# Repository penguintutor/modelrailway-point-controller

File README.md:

# Model railway point controller

The model railway point controller provides a way to control up to 4 points using a Raspberry Pi Pico W. It includes a MOSFET based capacitor discharge unit on the PCB and MOSFET controllers for each of the point motors.

It includes a second control board connected by I2C which can be connected to physical LEDs and switches to provide a way to control the points. The points can also be controlled using a web interface which can also be used in conjunction with GUI software to provide a touch screen interface.

# Installation

This version needs to be installed on a Raspberry Pi Pico W with the appropriate network enabled MicroPython. MicroPython can be installed through the Thonny editor.

To install the program, copy all the files in the pico-src directory to the top-level of the Raspberry Pi Pico. For the network connection you also need to create a file called secrets.py with details of your SSID and PASSWORD. The example below shows the formatting for the secrets.py file.

    SSID="NetworkSSID"
    PASSWORD="WiFiPassword"
    
## Configuration

The program can be run in two modes. 

* Access Point Mode (AP mode) - In this mode the Pico will act as a Wireless Access Point which you can connect to using another WiFi enabled device.
* Client Mode - In this mode you can connect to an existing wireless network

Note that in client mode it is currently blocking and will not operate until it has successfully connected to the network.

The mode is set by editing the entry "mode" in the pico-lights.py file. 

mode="ap"       # Use as an access point
mode="client"   # Use as a Wi-Fi client

## Running on startup

For the code to run automatically on start-up save the pico-point-controller.py file on your Pico as main.py.

## Using without the I2C control board

The board can be used in WiFi only mode, which does not use the I2C based switch and LED board. For that use the file pico-point-controller.wifionly.py instead of pico-point-controller.py (or save as main.py for auto-run) 

# More Information

For more details see [www.penguintutor.com/points](https://www.penguintutor.com/points)

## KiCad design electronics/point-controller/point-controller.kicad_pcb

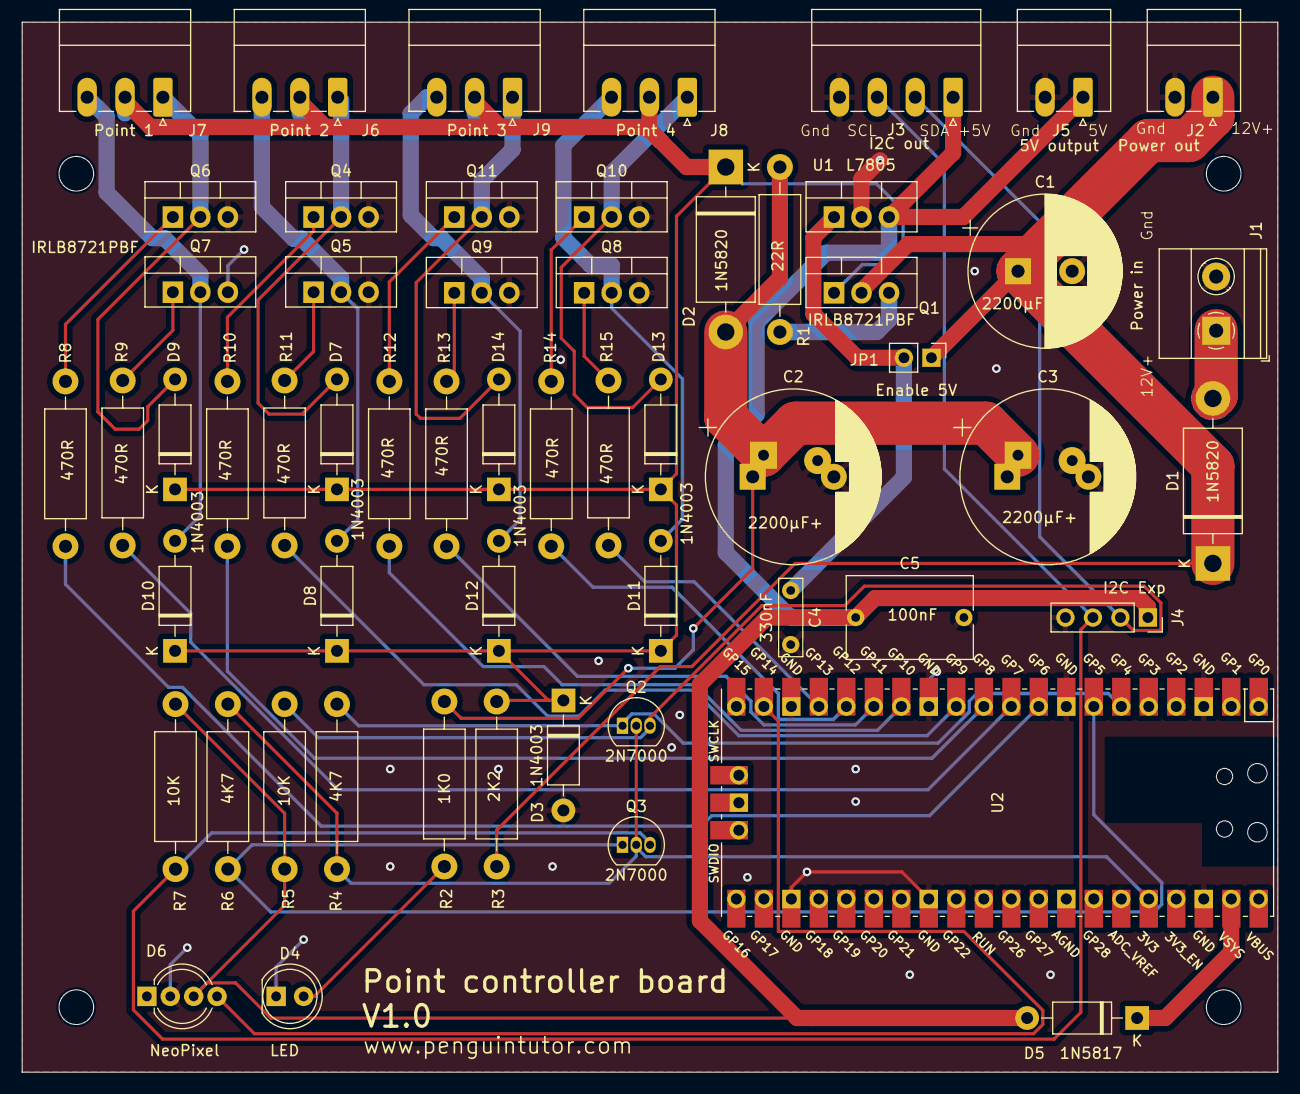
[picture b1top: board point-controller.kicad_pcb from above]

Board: 2 copper layers, 116.0 x 97.0 mm, 61 parts (0 on the bottom side), 40 nets.

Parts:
C1: 2200μF; CP_Radial_D14.0mm_P5.00mm
C2, C3: 2200μF+; CP_Radial_D16.0mm_P7.50mm_P5.00mm
C4: 330nF; C_Rect_L7.0mm_W2.0mm_P5.00mm
C5: 100nF; C_Rect_L11.5mm_W7.5mm_P10.00mm_MKT
D1, D2: 1N5820; D_DO-201AD_P15.24mm_Horizontal
D3, D7, D8, D9, D10, D11, D12, D13, D14: 1N4003; D_DO-41_SOD81_P10.16mm_Horizontal
D4: LED; LED_D5.0mm
D5: 1N5817; D_DO-41_SOD81_P10.16mm_Horizontal
D6: NeoPixel; LED_D5.0mm-4_RGB_Wide_Pins
H1, H2, H3, H4: MountingHole; MountingHole_3.2mm_M3
J1: Power in; TerminalBlock_Phoenix_MKDS-1,5-2_1x02_P5.00mm_Horizontal
J2: Power out; PhoenixContact_MC_1,5_2-G-3.5_1x02_P3.50mm_Horizontal
J3: I2C out; PhoenixContact_MC_1,5_4-G-3.5_1x04_P3.50mm_Horizontal
J4: I2C Exp; PinSocket_1x04_P2.54mm_Vertical
J5: 5V output; PhoenixContact_MC_1,5_2-G-3.5_1x02_P3.50mm_Horizontal
J6: Point 2; PhoenixContact_MC_1,5_3-G-3.5_1x03_P3.50mm_Horizontal
J7: Point 1; PhoenixContact_MC_1,5_3-G-3.5_1x03_P3.50mm_Horizontal
J8: Point 4; PhoenixContact_MC_1,5_3-G-3.5_1x03_P3.50mm_Horizontal
J9: Point 3; PhoenixContact_MC_1,5_3-G-3.5_1x03_P3.50mm_Horizontal
JP1: Enable 5V; PinHeader_1x02_P2.54mm_Vertical
Q1, Q4, Q5, Q6, Q7, Q8, Q9, Q10, Q11: IRLB8721PBF; TO-220-3_Vertical
Q2, Q3: 2N7000; TO-92_Inline
R1: 22R; R_Axial_DIN0411_L9.9mm_D3.6mm_P15.24mm_Horizontal
R2: 1K0; R_Axial_DIN0411_L9.9mm_D3.6mm_P15.24mm_Horizontal
R3: 2K2; R_Axial_DIN0411_L9.9mm_D3.6mm_P15.24mm_Horizontal
R4, R6: 4K7; R_Axial_DIN0411_L9.9mm_D3.6mm_P15.24mm_Horizontal
R5, R7: 10K; R_Axial_DIN0411_L9.9mm_D3.6mm_P15.24mm_Horizontal
R8, R9, R10, R11, R12, R13, R14, R15: 470R; R_Axial_DIN0411_L9.9mm_D3.6mm_P15.24mm_Horizontal
U1: L7805; TO-220-3_Vertical
U2: Pico; RPi_Pico_SMD_TH

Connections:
+3.3V: Q2.2 (G), Q3.2 (G), R4.1, R6.1, U2.36 (3V3)
+5V: C5.1, D5.2 (A), D6.3 (VDD), J3.1, J4.1, J5.1, R5.1, R7.1, U1.3 (OUT)
+12V: C1.1, D1.1 (K), J2.1, JP1.1 (A), Q1.2 (D), R3.1
CDU: D2.1 (K), D3.1 (K), D7.1 (K), D8.1 (K), D9.1 (K), D10.1 (K), D11.1 (K), D12.1 (K), D13.1 (K), D14.1 (K), J6.2, J7.2, J8.2, J9.2, Q1.1 (G), R3.2
GND: C1.2, C2.2, C3.2, C4.2, C5.2, D3.2 (A), D4.1 (K), D6.2 (GND), J1.2, J2.2, J3.4, J4.4, J5.2, Q4.3 (S), Q5.3 (S), Q6.3 (S), Q7.3 (S), Q8.3 (S), Q9.3 (S), Q10.3 (S), Q11.3 (S), U1.2 (GND), U2.3 (GND), U2.8 (GND), U2.13 (GND), U2.18 (GND), U2.23 (GND), U2.28 (GND), U2.38 (GND)
I2C 5V SCL: J3.3, J4.3, Q3.3 (D), R7.2
I2C 5V SDA: J3.2, J4.2, Q2.3 (D), R5.2
I2C SCL: Q3.1 (S), R6.2, U2.7 (GPIO5)
I2C SDA: Q2.1 (S), R4.2, U2.6 (GPIO4)
unnamed: D1.2 (A), J1.1
unnamed: C2.1, C3.1, D2.2 (A), R1.2, R2.1
unnamed: D4.2 (A), R2.2
unnamed: D5.1 (K), U2.39 (VSYS)
unnamed: D7.2 (A), J6.1, Q4.2 (D)
unnamed: D8.2 (A), J6.3, Q5.2 (D)
unnamed: D9.2 (A), J7.1, Q6.2 (D)
unnamed: D10.2 (A), J7.3, Q7.2 (D)
unnamed: D11.2 (A), J8.3, Q8.2 (D)
unnamed: D12.2 (A), J9.3, Q9.2 (D)
unnamed: D13.2 (A), J8.1, Q10.2 (D)
unnamed: D14.2 (A), J9.1, Q11.2 (D)
unnamed: C4.1, JP1.2 (B), U1.1 (IN)
unnamed: Q1.3 (S), R1.1
unnamed: Q4.1 (G), R10.2
unnamed: Q5.1 (G), R11.2
unnamed: Q6.1 (G), R8.2
unnamed: Q7.1 (G), R9.2
unnamed: Q8.1 (G), R15.2
unnamed: Q9.1 (G), R13.2
unnamed: Q10.1 (G), R14.2
unnamed: Q11.1 (G), R12.2
Point 1A: R8.1, U2.9 (GPIO6)
Point 1B: R9.1, U2.10 (GPIO7)
Point 2A: R10.1, U2.11 (GPIO8)
Point 2B: R11.1, U2.12 (GPIO9)
Point 3A: R12.1, U2.14 (GPIO10)
Point 3B: R13.1, U2.15 (GPIO11)
Point 4A: R14.1, U2.16 (GPIO12)
Point 4B: R15.1, U2.17 (GPIO13)
Status: D6.4 (DIN), U2.19 (GPIO14)

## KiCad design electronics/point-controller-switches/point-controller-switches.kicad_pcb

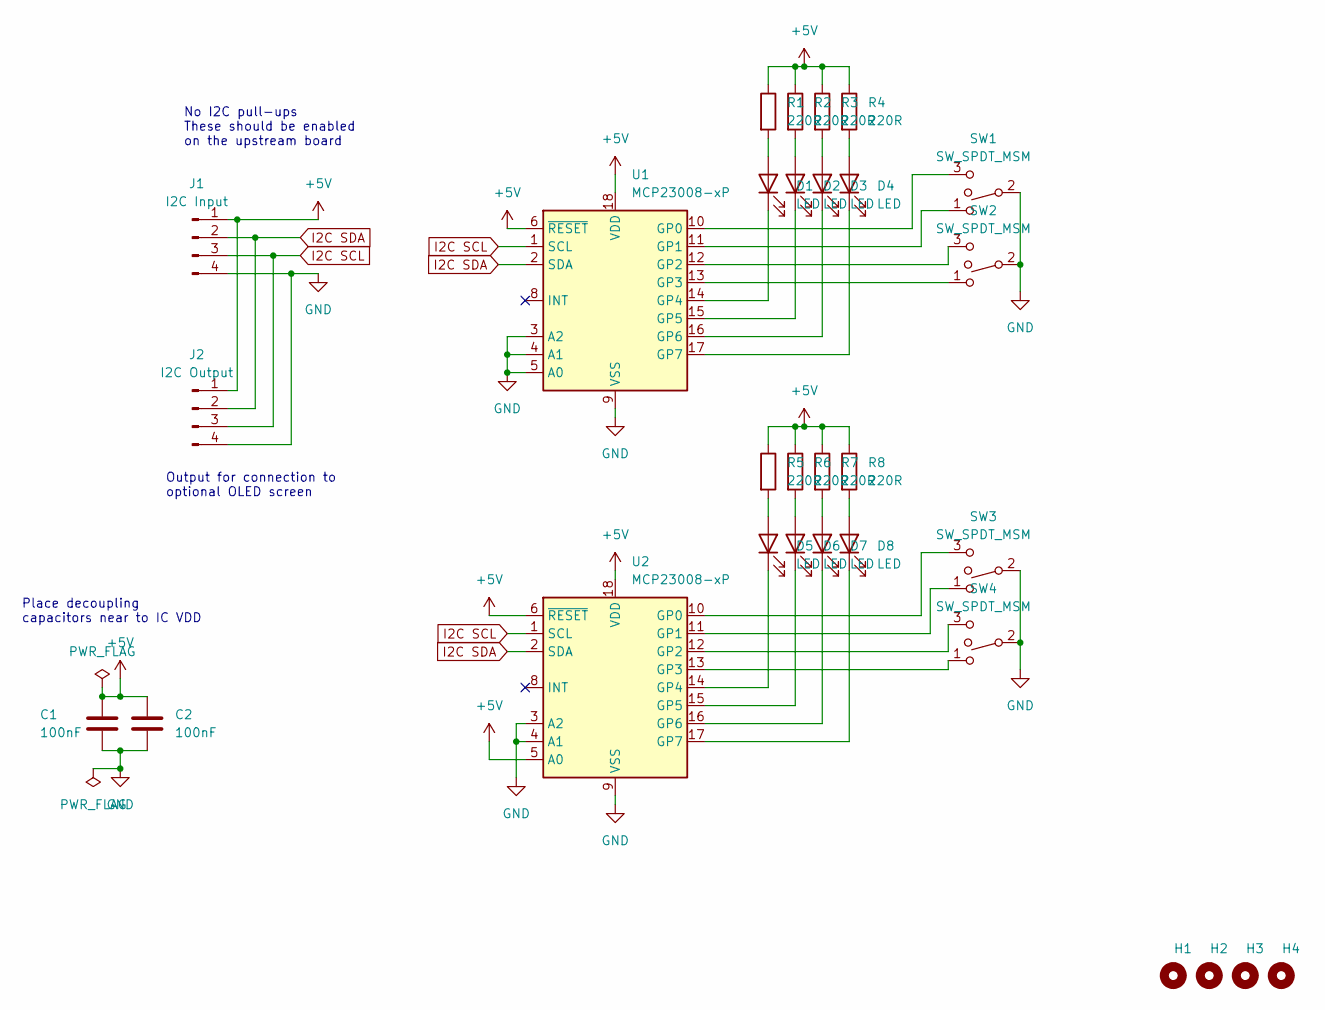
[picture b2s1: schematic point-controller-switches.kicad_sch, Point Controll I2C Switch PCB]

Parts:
C1, C2: 100nF; C_Disc_D4.3mm_W1.9mm_P5.00mm
D1, D2, D3, D4, D5, D6, D7, D8: LED; PinHeader_1x02_P2.54mm_Vertical
H1, H2, H3, H4: MountingHole; MountingHole_3.2mm_M3
J1: I2C Input; PinHeader_1x04_P2.54mm_Vertical
J2: I2C Output; PinHeader_1x04_P2.54mm_Vertical
R1, R2, R3, R4, R5, R6, R7, R8: 220R; R_Axial_DIN0207_L6.3mm_D2.5mm_P2.54mm_Vertical
SW1, SW2, SW3, SW4: SW_SPDT_MSM; PinHeader_1x03_P2.54mm_Vertical
U1, U2: MCP23008-xP; DIP-18_W7.62mm

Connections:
+5V: C1.1, C2.1, J1.1, J2.1, R1.1, R2.1, R3.1, R4.1, R5.1, R6.1, R7.1, R8.1, U1.6 (~RESET), U1.18 (VDD), U2.5 (A0), U2.6 (~RESET), U2.18 (VDD)
GND: C1.2, C2.2, J1.4, J2.4, SW1.2, SW2.2, SW3.2, SW4.2, U1.3 (A2), U1.4 (A1), U1.5 (A0), U1.9 (VSS), U2.3 (A2), U2.4 (A1), U2.9 (VSS)
I2C SCL: J1.3, J2.3, U1.1 (SCL), U2.1 (SCL)
I2C SDA: J1.2, J2.2, U1.2 (SDA), U2.2 (SDA)
unnamed: D1.2 (A), R1.2
unnamed: D1.1 (K), U1.14 (GP4)
unnamed: D2.2 (A), R2.2
unnamed: D2.1 (K), U1.15 (GP5)
unnamed: D3.2 (A), R3.2
unnamed: D3.1 (K), U1.16 (GP6)
unnamed: D4.2 (A), R4.2
unnamed: D4.1 (K), U1.17 (GP7)
unnamed: D5.2 (A), R5.2
unnamed: D5.1 (K), U2.14 (GP4)
unnamed: D6.2 (A), R6.2
unnamed: D6.1 (K), U2.15 (GP5)
unnamed: D7.2 (A), R7.2
unnamed: D7.1 (K), U2.16 (GP6)
unnamed: D8.2 (A), R8.2
unnamed: D8.1 (K), U2.17 (GP7)
unnamed: SW1.3, U1.10 (GP0)
unnamed: SW1.1, U1.11 (GP1)
unnamed: SW2.3, U1.12 (GP2)
unnamed: SW2.1, U1.13 (GP3)
unnamed: SW3.3, U2.10 (GP0)
unnamed: SW3.1, U2.11 (GP1)
unnamed: SW4.3, U2.12 (GP2)
unnamed: SW4.1, U2.13 (GP3)

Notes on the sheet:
Place decoupling capacitors near to IC VDD
Output for connection to optional OLED screen
No I2C pull-ups These should be enabled on the upstream board

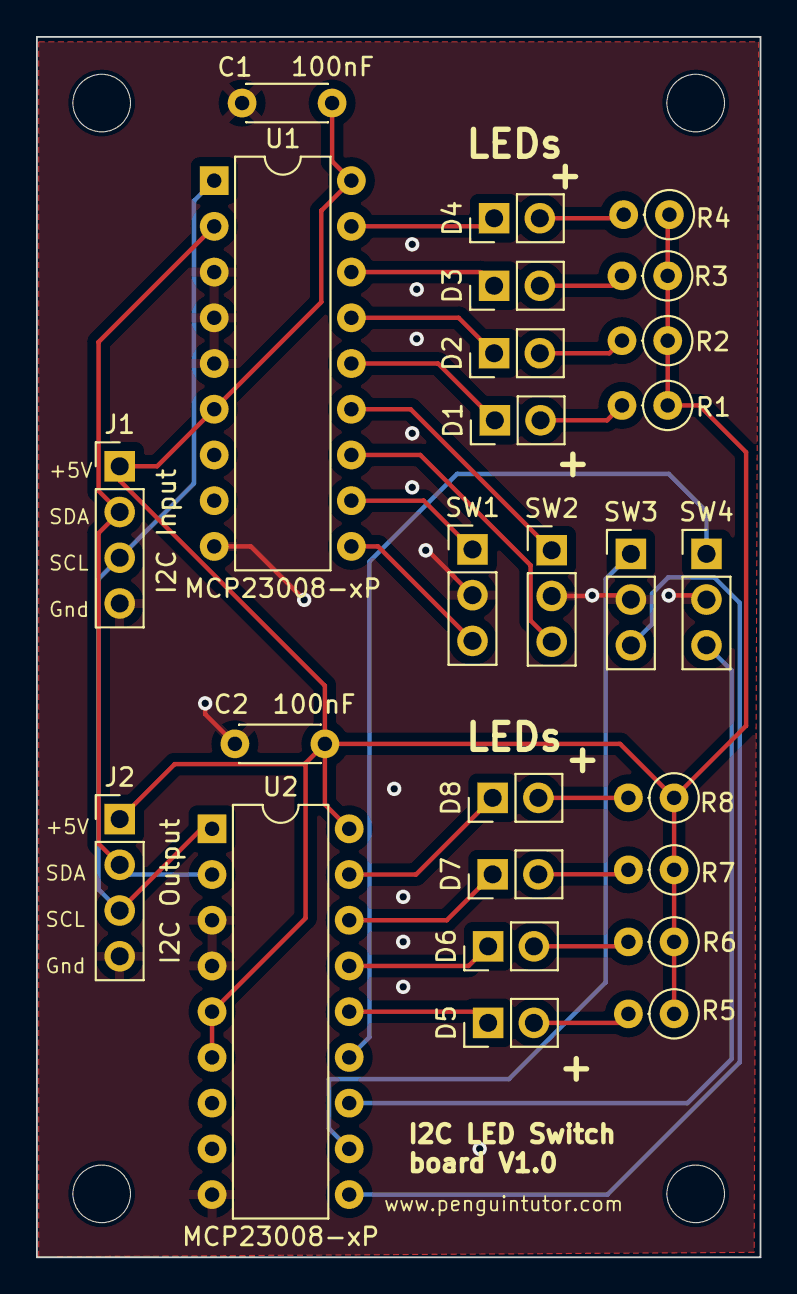
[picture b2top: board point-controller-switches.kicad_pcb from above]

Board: 2 copper layers, 40.2 x 67.8 mm, 30 parts (0 on the bottom side), 28 nets.

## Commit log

2024-04-30 Initial version for Pico W
2024-04-30 Add link to website
2024-04-30 Correct markdown
2024-06-09 Add alternative wifionly version to allow testing of main board without i2c board
2024-06-09 bug fix for point numbering
2025-01-01 Add WiFi only alternative version
2025-01-01 Add electronics circuit design files
2025-01-01 Add electronics files
2025-01-01 Add initial enclosure design
2025-01-01 Add initial design for interface only PCB
2025-01-02 Add enclosure files with engraving / etch details
